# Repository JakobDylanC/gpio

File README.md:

# gpio
GPIO to Breadboard Adapter

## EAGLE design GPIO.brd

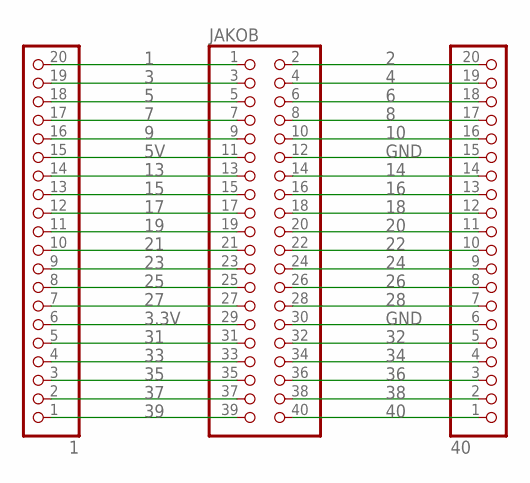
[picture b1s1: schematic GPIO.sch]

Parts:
1, 40: PINHD-1X20; 1X20
JAKOB: PINHD-2X20; 2X20

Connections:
1: 1.20, JAKOB.1
2: 40.20, JAKOB.2
3: 1.19, JAKOB.3
3.3V: 1.6, JAKOB.29
4: 40.19, JAKOB.4
5: 1.18, JAKOB.5
5V: 1.15, JAKOB.11
6: 40.18, JAKOB.6
7: 1.17, JAKOB.7
8: 40.17, JAKOB.8
9: 1.16, JAKOB.9
10: 40.16, JAKOB.10
13: 1.14, JAKOB.13
14: 40.14, JAKOB.14
15: 1.13, JAKOB.15
16: 40.13, JAKOB.16
17: 1.12, JAKOB.17
18: 40.12, JAKOB.18
19: 1.11, JAKOB.19
20: 40.11, JAKOB.20
21: 1.10, JAKOB.21
22: 40.10, JAKOB.22
23: 1.9, JAKOB.23
24: 40.9, JAKOB.24
25: 1.8, JAKOB.25
26: 40.8, JAKOB.26
27: 1.7, JAKOB.27
28: 40.7, JAKOB.28
31: 1.5, JAKOB.31
32: 40.5, JAKOB.32
33: 1.4, JAKOB.33
34: 40.4, JAKOB.34
35: 1.3, JAKOB.35
36: 40.3, JAKOB.36
37: 1.2, JAKOB.37
38: 40.2, JAKOB.38
39: 1.1, JAKOB.39
40: 40.1, JAKOB.40
GND: 40.6, 40.15, JAKOB.12, JAKOB.30

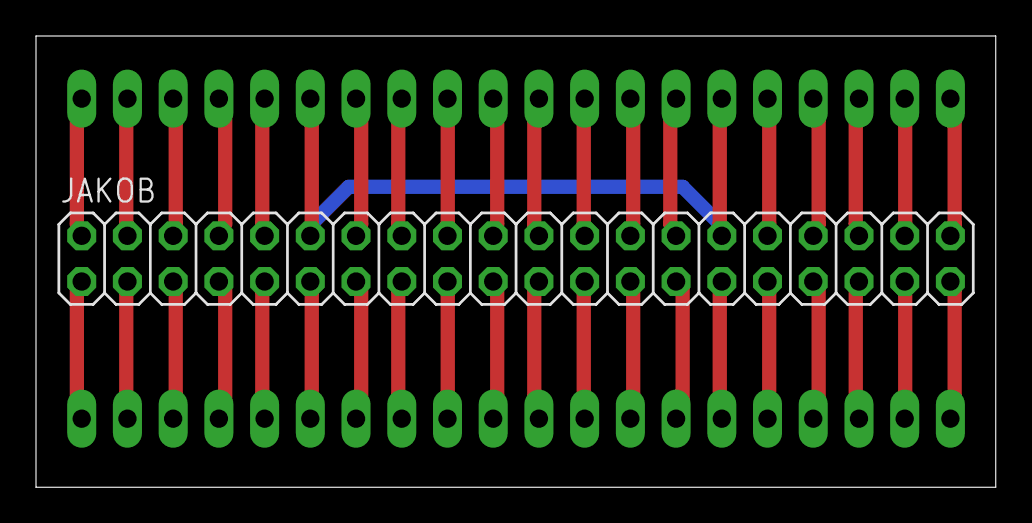
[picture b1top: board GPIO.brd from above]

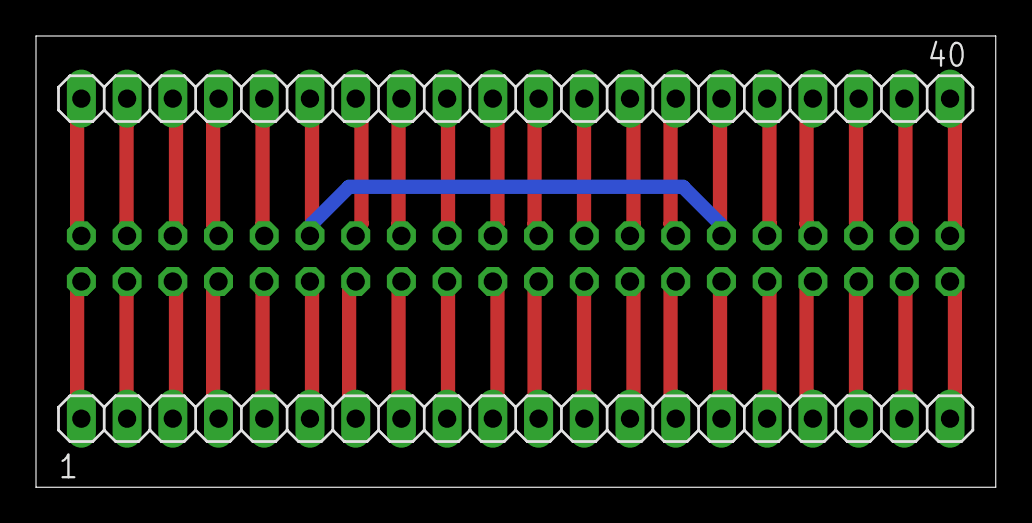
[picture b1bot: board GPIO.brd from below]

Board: 2 copper layers, 53.3 x 25.1 mm, 3 parts (2 on the bottom side), 39 nets.

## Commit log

2018-04-24 Main board and schematic files uploaded
